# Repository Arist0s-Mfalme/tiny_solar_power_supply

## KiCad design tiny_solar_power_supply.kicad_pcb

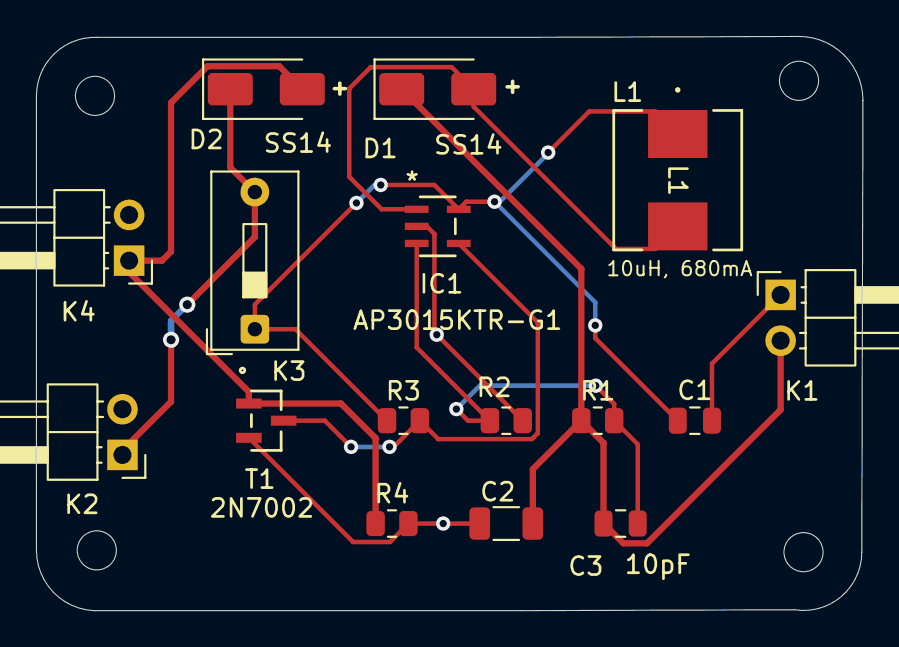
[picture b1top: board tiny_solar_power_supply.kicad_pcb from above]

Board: 2 copper layers, 45.9 x 31.9 mm, 16 parts (0 on the bottom side), 8 nets.

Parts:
C1: 4.7uF; C_0805_2012Metric
C2: 22uF; C_1206_3216Metric
C3: 10pF; C_0805_2012Metric
D1, D2: SS14; D_SMA
IC1: AP3015KTR-G1; SOT-23-5_AP3015_DIO
K1, K2, K4: Conn_01x02_Pin; PinHeader_1x02_P2.54mm_Horizontal
K3: Conn_01x02_Pin; SW_DIP_SPSTx01_Slide_9.78x4.72mm_W7.62mm_P2.54mm
L1: 10uH, 680mA; IND_ASPI-0630LR_ABR
R1, R4: 1M; R_0805_2012Metric
R2: 604k; R_0805_2012Metric
R3: 10k; R_0805_2012Metric
T1: 2N7002; SOT-23_ONS

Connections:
/BAT_P: D2.1 (K), K2.1, K3.2
/OUT_P: C2.1, C3.1, D1.1 (K), K1.2, R1.1
/SOLAR_P: D2.2 (A), K4.1, R4.1, T1.1 (G)
GNDD: C1.2, C2.2, IC1.2 (GND), K1.1, K2.2, K4.2, R2.1, R4.2, T1.2 (S)
unnamed: D1.2 (A), IC1.1 (SW), L1.2
unnamed: IC1.4 (*SHDN), R3.2, T1.3 (D)
unnamed: C3.2, IC1.3 (FB), R1.2, R2.2
unnamed: C1.1, IC1.5 (VIN), K3.1, L1.1, R3.1
